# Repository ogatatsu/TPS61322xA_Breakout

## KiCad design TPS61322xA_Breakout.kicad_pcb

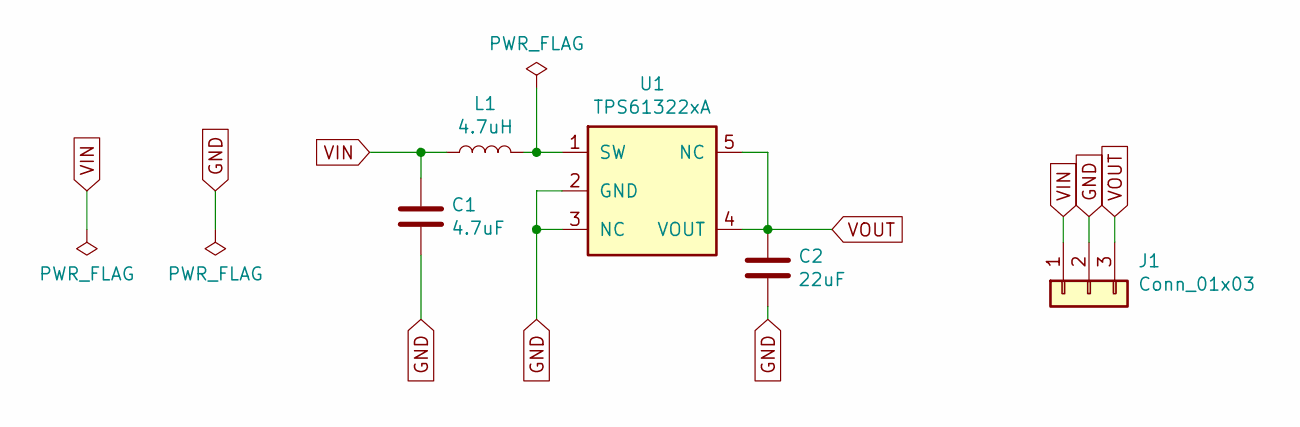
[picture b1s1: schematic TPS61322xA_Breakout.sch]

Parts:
C1: 4.7uF; C_0603_1608Metric_Pad1.05x0.95mm_HandSolder
C2: 22uF; C_0603_1608Metric_Pad1.05x0.95mm_HandSolder
J1: Conn_01x03; Connector_2.54mm_03
L1: 4.7uH; L_1210_3225Metric
U1: TPS61322xA; SOT-23-5_HandSoldering

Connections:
GND: C1.2, C2.2, J1.2, U1.2 (GND), U1.3 (NC)
unnamed: L1.2, U1.1 (SW)
VIN: C1.1, J1.1, L1.1
VOUT: C2.1, J1.3, U1.4 (VOUT), U1.5 (NC)

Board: 2 copper layers, 5 parts (0 on the bottom side), 4 nets, no tracks yet.

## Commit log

2020-11-08 add schematic
